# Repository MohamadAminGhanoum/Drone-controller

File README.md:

# Drone-controller
So i have this drone that i have had for a very long time. I recieved it without a controller, so it was basically a uselss drone. I played with it previously and tried to connect all 4 motors to 5v to see if it would fly, but ofc it wouldnt stablilize and all that. Today i know that i need a specific IMU snesor using the gyroscope to determing how the drone is positioned, and then it would send this signal to a chip that would control the current or power recieved by each motor to stabilize the drone. This is what i have planned to make in this project, and it would be slightly more complex than a normal drone controller, as i need to add motor controllers as well because my drone has bruhless motors.

## Schematics for controller:

## Schematics for remote:

## PCB for controller:

## PCB for remote:

## 3d shape for controller:

## 3d shape for remote:

## BOM:

|Nr |Designator                                                      |Footprint                                                          |Quantity                 |Cost, usd|Designation                |Supplier and ref|Link                                                                                                                                                                                                                                                        |
|---|----------------------------------------------------------------|-------------------------------------------------------------------|-------------------------|---------|---------------------------|----------------|------------------------------------------------------------------------------------------------------------------------------------------------------------------------------------------------------------------------------------------------------------|
|1  |U1                                                              |LQFP-64_10x10mm_P0.5mm                                             |3                        |20.86    |STM32F405RGTx              |Lcsc            |https://www.lcsc.com/product-detail/C15742.html?spm=wm.gwc.xh.0.tp___wm.sy.ssl.gwc&lcsc_vid=EQBXBlEAQgcKBVQCEVVYVVZWFAJcV1dXFlJYUFxeRgIxVlNeQ1ddUFZfTlFaVzsOAxUeFF5JWBEPFBcWGBMaSQgFBAJABAsLWA%3D%3D                                                        |
|2  |Fan1,2,3,4                                                      |JST_PH_B2B-PH-K_1x02_P2.00mm_Vertical                              |20                       |0.71     |MOTORs                     |LCSC            |https://www.lcsc.com/product-detail/C131337.html?s_z=n_q_p_JST_PH_B2B-PH-K_1x02_P2.00mm_Vertical&spm=wm.ssy.bg.0.stp&lcsc_vid=EQBXBlEAQgcKBVQCEVVYVVZWFAJcV1dXFlJYUFxeRgIxVlNeQ1ZfUlxSRVJWVjsOAxUeFF5JWBYZEEoKFBINSQcJGk4%3D                                |
|3  |R5,R6                                                           |R_0603_1608Metric                                                  |100                      |0.72     |22                         |LCSC            |https://www.lcsc.com/product-detail/C107701.html?s_z=n_q_t_22ohm%25200603&spm=wm.fly.bg.0.stp___wm.ssy.tc.0.tz&lcsc_vid=EQBXBlEAQgcKBVQCEVVYVVZWFAJcV1dXFlJYUFxeRgIxVlNeQ1ZfUlxfQVZYXjsOAxUeFF5JWBYZEEoKFBINSQcJGk4dAgUUFAk%3D                              |
|4  |L2                                                              |L_Bourns_SRP7028A_7.3x6.6mm                                        |10                       |0.8      |15uH                       |LCSC            |https://www.lcsc.com/product-detail/C5349699.html?spm=wm.gwc.xh.5.tp___wm.sy.ssl.gwc&lcsc_vid=EQBXBlEAQgcKBVQCEVVYVVZWFAJcV1dXFlJYUFxeRgIxVlNeQ1ddUFZfTlFaVzsOAxUeFF5JWBEPFBcWGBMaSQgFBAJABAsLWA%3D%3D                                                      |
|5  |C3,C32,C10,C17,C30,C18,C21,C23,C20,C9,C29,C26,C22,C19,C7,C24,C25|C_0603_1608Metric                                                  |50                       |1.27     |0.1uF                      |LCSC            |https://www.lcsc.com/product-detail/C14663.html?s_z=n_q_t_0.1uF%25200603&spm=wm.fly.bg.0.stp___wm.ssy.tc.0.tz&lcsc_vid=EQBXBlEAQgcKBVQCEVVYVVZWFAJcV1dXFlJYUFxeRgIxVlNeQ1ZfUVdVRlFcVzsOAxUeFF5JWBYZEEoKFBINSQcJGk4eFQsCAgIaSgADAwAHC0slTlNaV1VIHxUDCw%3D%3D |
|6  |C31,C33                                                         |C_0603_1608Metric                                                  |50                       |0.8      |10nF                       |LCSC            |https://www.lcsc.com/product-detail/C100042.html?s_z=n_q_t_10nF%25200603&spm=wm.fly.bg.0.stp___wm.ssy.tc.0.tz&lcsc_vid=EQBXBlEAQgcKBVQCEVVYVVZWFAJcV1dXFlJYUFxeRgIxVlNeQ1ZfUVdQQ1RXUDsOAxUeFF5JWBYZEEoKFBINSQcJGk4NBhADEA4cHktXRlVcSQwSGg0%3D               |
|7  |U7                                                              |XCVR_SX1280IMLTRT                                                  |3                        |12.71    |SX1280IMLTRT               |LCSC            |https://www.lcsc.com/product-detail/C125969.html?spm=wm.gwc.xh.4.tp___wm.sy.ssl.gwc&lcsc_vid=EQBXBlEAQgcKBVQCEVVYVVZWFAJcV1dXFlJYUFxeRgIxVlNeQ1ddUFZfTlFaVzsOAxUeFF5JWBEPFBcWGBMaSQgFBAJABAsLWA%3D%3D                                                       |
|8  |C39                                                             |C_0603_1608Metric                                                  |50                       |0.73     |100pF                      |LCSC            |https://www.lcsc.com/product-detail/C14665.html?s_z=n_q_t_100pF%25200603&spm=wm.fly.bg.0.stp___wm.ssy.tc.0.tz&lcsc_vid=EQBXBlEAQgcKBVQCEVVYVVZWFAJcV1dXFlJYUFxeRgIxVlNeQ1ZfUVdfQlNZXjsOAxUeFF5JWBYZEEoKFBINSQcJGk4eFQsCAgIaSgADAwAHC0slRlFeV1BUWQkaCgg%3D   |
|9  |C34                                                             |C_0603_1608Metric                                                  |20                       |0.62     |470nF                      |LCSC            |https://www.lcsc.com/product-detail/C1623.html?s_z=n_q_t_470nF%25200603&spm=wm.fly.bg.0.stp___wm.ssy.tc.0.tz&lcsc_vid=EQBXBlEAQgcKBVQCEVVYVVZWFAJcV1dXFlJYUFxeRgIxVlNeQ1ZfUVBURFhWVzsOAxUeFF5JWBYZEEoKFBINSQcJGk4dAgUUFAk%3D                                |
|10 |C2,C1,C12,C15                                                   |C_0603_1608Metric                                                  |20                       |0.83     |10uF                       |LCSC            |https://www.lcsc.com/product-detail/C19702.html?s_z=n_q_t_10uF%25200603&spm=wm.fly.bg.0.stp___wm.ssy.tc.0.tz&lcsc_vid=EQBXBlEAQgcKBVQCEVVYVVZWFAJcV1dXFlJYUFxeRgIxVlNeQ1ZfUVBTQlVXUjsOAxUeFF5JWBYZEEoKFBINSQcJGk4eFQsCAgIaSgADAwAHC0slRldcVEoOAwwC          |
|11 |C6,C4,C5                                                        |C_0603_1608Metric                                                  |5                        |0.66     |22uF                       |LCSC            |https://www.lcsc.com/product-detail/C2762594.html?s_z=n_q_t_22uf%25200603&spm=wm.fly.bg.0.stp___wm.ssy.tc.0.tz&lcsc_vid=EQBXBlEAQgcKBVQCEVVYVVZWFAJcV1dXFlJYUFxeRgIxVlNeQ1ZfUVBfQ1VZUTsOAxUeFF5JWBYZEEoKFBINSQcJGk4eFQsCAgIaSgADAwAHC0slRlhZV1ZIHxUDCw%3D%3D|
|12 |U5                                                              |SOT-23-6                                                           |3                        |4        |TPS563200                  |LCSC            |https://www.lcsc.com/product-detail/C97253.html?spm=wm.gwc.xh.2.tp___wm.sy.ssl.gwc&lcsc_vid=EQBXBlEAQgcKBVQCEVVYVVZWFAJcV1dXFlJYUFxeRgIxVlNeQ1ddUFZfTlFaVzsOAxUeFF5JWBEPFBcWGBMaSQgFBAJABAsLWA%3D%3D                                                        |
|13 |C35                                                             |C_0603_1608Metric                                                  |5                        |0.76     |0.8pF                      |LCSC            |https://www.lcsc.com/product-detail/C42432054.html?s_z=n_q_t_0.8pF%25200603&spm=wm.fly.bg.0.stp&lcsc_vid=EQBXBlEAQgcKBVQCEVVYVVZWFAJcV1dXFlJYUFxeRgIxVlNeQ1ZfUVFVRFBaUTsOAxUeFF5JWBYZEEoKFBINSQcJGk4dAgUUFAk%3D                                             |
|14 |U4,U3                                                           |HTSSOP-16-1EP_4.4x5mm_P0.65mm_EP3.4x5mm_Mask2.46x2.31mm_ThermalVias|3                        |3.27     |DRV8833PWP                 |LCSC            |https://www.lcsc.com/product-detail/C50506.html?spm=wm.gwc.dh.1.tp___wm.sy.ssl.gwc&lcsc_vid=EQBXBlEAQgcKBVQCEVVYVVZWFAJcV1dXFlJYUFxeRgIxVlNeQ1ddUFZfTlFaVzsOAxUeFF5JWBEPFBcWGBMaSQgFBAJABAsLWA%3D%3D                                                        |
|15 |J1                                                              |USB_C_Receptacle_GCT_USB4105-xx-A_16P_TopMnt_Horizontal            |2                        |0        |USB_C_Receptacle_USB2.0_16P|Selfsourced     |previously bought from lcsc                                                                                                                                                                                                                                 |
|16 |C16,C11                                                         |C_0603_1608Metric                                                  |50                       |0.8      |0.01uF                     |LCSC            |https://www.lcsc.com/product-detail/C100042.html?s_z=n_q_t_0.01uF%25200603&spm=wm.fly.bg.0.stp&lcsc_vid=EQBXBlEAQgcKBVQCEVVYVVZWFAJcV1dXFlJYUFxeRgIxVlNeQ1ZfUVFQRFBeXjsOAxUeFF5JWBYZEEoKFBINSQcJGk4dAgUUFAk%3D                                              |
|17 |C13,C14,C28                                                     |C_0603_1608Metric                                                  |50                       |1.45     |2.2uF                      |LCSC            |https://www.lcsc.com/product-detail/C23630.html?s_z=n_q_t_2.2uF%25200603&spm=wm.fly.bg.0.stp___wm.ssy.tc.0.tz&lcsc_vid=EQBXBlEAQgcKBVQCEVVYVVZWFAJcV1dXFlJYUFxeRgIxVlNeQ1ZfUVFeQlZZVzsOAxUeFF5JWBYZEEoKFBINSQcJGk4eFQsCAgIaSgADAwAHC0slRlFeV1BUWQkaCgg%3D   |
|18 |R3,R4                                                           |R_0603_1608Metric                                                  |100                      |0.28     |5.1k                       |LCSC            |https://www.lcsc.com/product-detail/C2907044.html?s_z=n_q_t_5.1k%25200603&spm=wm.fly.bg.0.stp___wm.ssy.tc.0.tz&lcsc_vid=EQBXBlEAQgcKBVQCEVVYVVZWFAJcV1dXFlJYUFxeRgIxVlNeQ1ZfUVJXQ1FdVDsOAxUeFF5JWBYZEEoKFBINSQcJGk4NBhADEA4cHktXRlVcSQwSGg0%3D              |
|19 |R7,R2                                                           |R_0603_1608Metric                                                  |100                      |0.81     |10k                        |LCSC            |https://www.lcsc.com/product-detail/C844918.html?s_z=n_q_t_10k%25200603&spm=wm.fly.bg.0.stp___wm.ssy.tc.0.tz&lcsc_vid=EQBXBlEAQgcKBVQCEVVYVVZWFAJcV1dXFlJYUFxeRgIxVlNeQ1ZfUVJSRFhbUzsOAxUeFF5JWBYZEEoKFBINSQcJGk4NBhADEA4cHktXRlhXSQwSGg0%3D                |
|21 |C27                                                             |C_0603_1608Metric                                                  |50                       |1.15     |1uF                        |LCSC            |https://www.lcsc.com/product-detail/C29936.html?s_z=n_q_t_1uF%25200603&spm=wm.fly.bg.0.stp&lcsc_vid=EQBXBlEAQgcKBVQCEVVYVVZWFAJcV1dXFlJYUFxeRgIxVlNeQ1ZfUVJfRVFbXzsOAxUeFF5JWBYZEEoKFBINSQcJGk4dAgUUFAk%3D                                                  |
|22 |D1,D2                                                           |D_SMA                                                              |50                       |0.73     |SS14                       |LCSC            |https://www.lcsc.com/product-detail/C2837270.html?s_z=n_q_x_SS14&spm=wm.ssy.em.0.tz&lcsc_vid=EQBXBlEAQgcKBVQCEVVYVVZWFAJcV1dXFlJYUFxeRgIxVlNeQ1ZfUVNUQFFeVzsOAxUeFF5JWBYZEEoKFBINSQcJGk4NBhADEA4cHktXRlVcSQwSGg0%3D                                         |
|23 |C38                                                             |C_0603_1608Metric                                                  |100                      |0.72     |0.5pF                      |LCSC            |https://www.lcsc.com/product-detail/C1633.html?s_z=n_q_t_0.5pf%25200603&spm=wm.fly.bg.0.stp&lcsc_vid=EQBXBlEAQgcKBVQCEVVYVVZWFAJcV1dXFlJYUFxeRgIxVlNeQ1ZfUVNQRFNWUDsOAxUeFF5JWBYZEEoKFBINSQcJGk4dAgUUFAk%3D                                                 |
|24 |Y2                                                              |Crystal_SMD_3225-4Pin_3.2x2.5mm                                    |5                        |0.51     |52mhz                      |LCSC            |https://www.lcsc.com/product-detail/C3034316.html?s_z=n_q_52%2520mhz%2520crystal&spm=wm.fly.bg.0.stp&lcsc_vid=T1FYAQdRRlJYVlZTQldcX11eQ1FfUlFUElBWUQFVQgIxVlNeQlVWV11eRFZXUzsOAxUeFF5JWBYZEEoKFBINSQcJGk4eFQsCAgIaSgADAwAHC0slQFBWUVFfWQkaCgg%3D            |
|25 |AE1                                                             |U.FL_Hirose_U.FL-R-SMT-1_Vertical                                  |1                        |N/A      |Antenna                    |N/A             |https://www.lcsc.com/product-detail/C88374.html                                                                                                                                                                                                             |
|26 |JBat                                                            |JST_PH_B2B-PH-K_1x02_P2.00mm_Vertical                              |20                       |0.71     |Battery_connector          |LCSC            |https://www.lcsc.com/product-detail/C131337.html?s_z=n_q_p_JST_PH_B2B-PH-K_1x02_P2.00mm_Vertical&spm=wm.ssy.bg.0.stp&lcsc_vid=EQBXBlEAQgcKBVQCEVVYVVZWFAJcV1dXFlJYUFxeRgIxVlNeQ1ZfUlxSRVJWVjsOAxUeFF5JWBYZEEoKFBINSQcJGk4%3D                                |
|27 |L1                                                              |L_Bourns_SRP7028A_7.3x6.6mm                                        |10                       |0.7      |3.3uH                      |LCSC            |https://www.lcsc.com/product-detail/C5349703.html?s_z=n_q_p_3.3uH%25207.1x6.6&spm=wm.ssy.bg.0.stp&lcsc_vid=EQBXBlEAQgcKBVQCEVVYVVZWFAJcV1dXFlJYUFxeRgIxVlNeQ1ZfUV1WR1BWXjsOAxUeFF5JWBYZEEoKFBINSQcJGk4NBhADEA4cHktXRlRbSQwSGg0%3D                           |
|28 |R1                                                              |R_0603_1608Metric                                                  |100                      |0.32     |54.9k                      |LCSC            |https://www.lcsc.com/product-detail/C23077.html?s_z=n_q_p_54.9k%252006043&spm=wm.ssy.bg.1.stp&lcsc_vid=EQBXBlEAQgcKBVQCEVVYVVZWFAJcV1dXFlJYUFxeRgIxVlNeQ1ZfUV1VQVRXUDsOAxUeFF5JWBYZEEoKFBINSQcJGk4eFQsCAgIaSgADAwAHC0slQlJaXlNWRE8GEwkK                     |
|29 |SW1                                                             |R_0603_1608Metric                                                  |1                        |0        |SW_Push                    |Selfsourced     |previously bought from lcsc                                                                                                                                                                                                                                 |
|30 |U6                                                              |SOT95P285X140-5N                                                   |5                        |0.79     |AP2112K-3.3TRG1            |LCSC            |https://www.lcsc.com/product-detail/C51118.html?spm=wm.gwc.xh.3.tp___wm.sy.ssl.gwc&lcsc_vid=EQBXBlEAQgcKBVQCEVVYVVZWFAJcV1dXFlJYUFxeRgIxVlNeQ1ddUFZfTlFaVzsOAxUeFF5JWBEPFBcWGBMaSQgFBAJABAsLWA%3D%3D                                                        |
|31 |U2                                                              |InvenSense_QFN-24_4x4mm_P0.5mm                                     |2                        |29.24    |MPU-6000                   |LCSC            |https://www.lcsc.com/product-detail/C92401.html?s_z=n_q_x_MPU-6000&spm=wm.ssy.em.0.tz&lcsc_vid=EQBXBlEAQgcKBVQCEVVYVVZWFAJcV1dXFlJYUFxeRgIxVlNeQ1ZfUVZSQ1laVTsOAxUeFF5JWBYZEEoKFBINSQcJGk4NBhYS                                                             |
|32 |C8                                                              |C_0603_1608Metric                                                  |50                       |0.63     |2.2nF                      |LCSC            |https://www.lcsc.com/product-detail/C16033.html?s_z=n_q_t_2.2nF%25200603&spm=wm.fly.bg.0.stp___wm.ssy.tc.0.tz&lcsc_vid=EQBXBlEAQgcKBVQCEVVYVVZWFAJcV1dXFlJYUFxeRgIxVlNeQ1ZfUV1QQlRZVDsOAxUeFF5JWBYZEEoKFBINSQcJGk4eFQsCAgIaSgADAwAHC0slRVJeUFNIHxUDCw%3D%3D |
|33 |C37,C36                                                         |C_0603_1608Metric                                                  |100                      |0.68     |1.2pF                      |LCSC            |https://www.lcsc.com/product-detail/C519098.html?s_z=n_q_t_1.2pF%25200603&spm=wm.fly.bg.0.stp___wm.ssy.tc.0.tz&lcsc_vid=EQBXBlEAQgcKBVQCEVVYVVZWFAJcV1dXFlJYUFxeRgIxVlNeQ1ZfUFRWRlBWVDsOAxUeFF5JWBYZEEoKFBINSQcJGk4eFQsCAgIaSgADAwAHC0slRldeVFdIHxUDCw%3D%3D|
|34 |PCB                                                             |Remote controller                                                  |5                        |7        |N/A                        |Jlcpcb          |N/A                                                                                                                                                                                                                                                         |
|35 |PCB                                                             |Drone controller                                                   |5                        |7        |N/A                        |Jlcpcb          |N/A                                                                                                                                                                                                                                                         |
|36 |AE1                                                             |Antenna                                                            |2                        |6.43     |N/A                        |LCSC            |https://www.lcsc.com/product-detail/C3285086.html                                                                                                                                                                                                           |
|37 |C                                                               |C_0603_1608Metric                                                  |50                       |0.7      |15pf                       |LCSC            |https://www.lcsc.com/product-detail/C1644.html?s_z=n_q_t_15pf%25200603&spm=wm.fly.bg.0.stp___wm.ssy.tc.0.tz&lcsc_vid=T1FYAQdRRlJYVlZTQldcX11eQ1FfUlFUElBWUQFVQgIxVlNeQlVXV1ReRlVXVTsOAxUeFF5JWBYZEEoKFBINSQcJGk4eFQsCAgIaSgADAwAHC0slRFNWUlReQU8GEwkK       |
|   |                                                                |                                                                   |                         |         |                           |                |                                                                                                                                                                                                                                                            |
|   |                                                                |                                                                   |Total price w. tax & ship|150.69   |                           |                |                                                                                                                                                                                                                                                            |

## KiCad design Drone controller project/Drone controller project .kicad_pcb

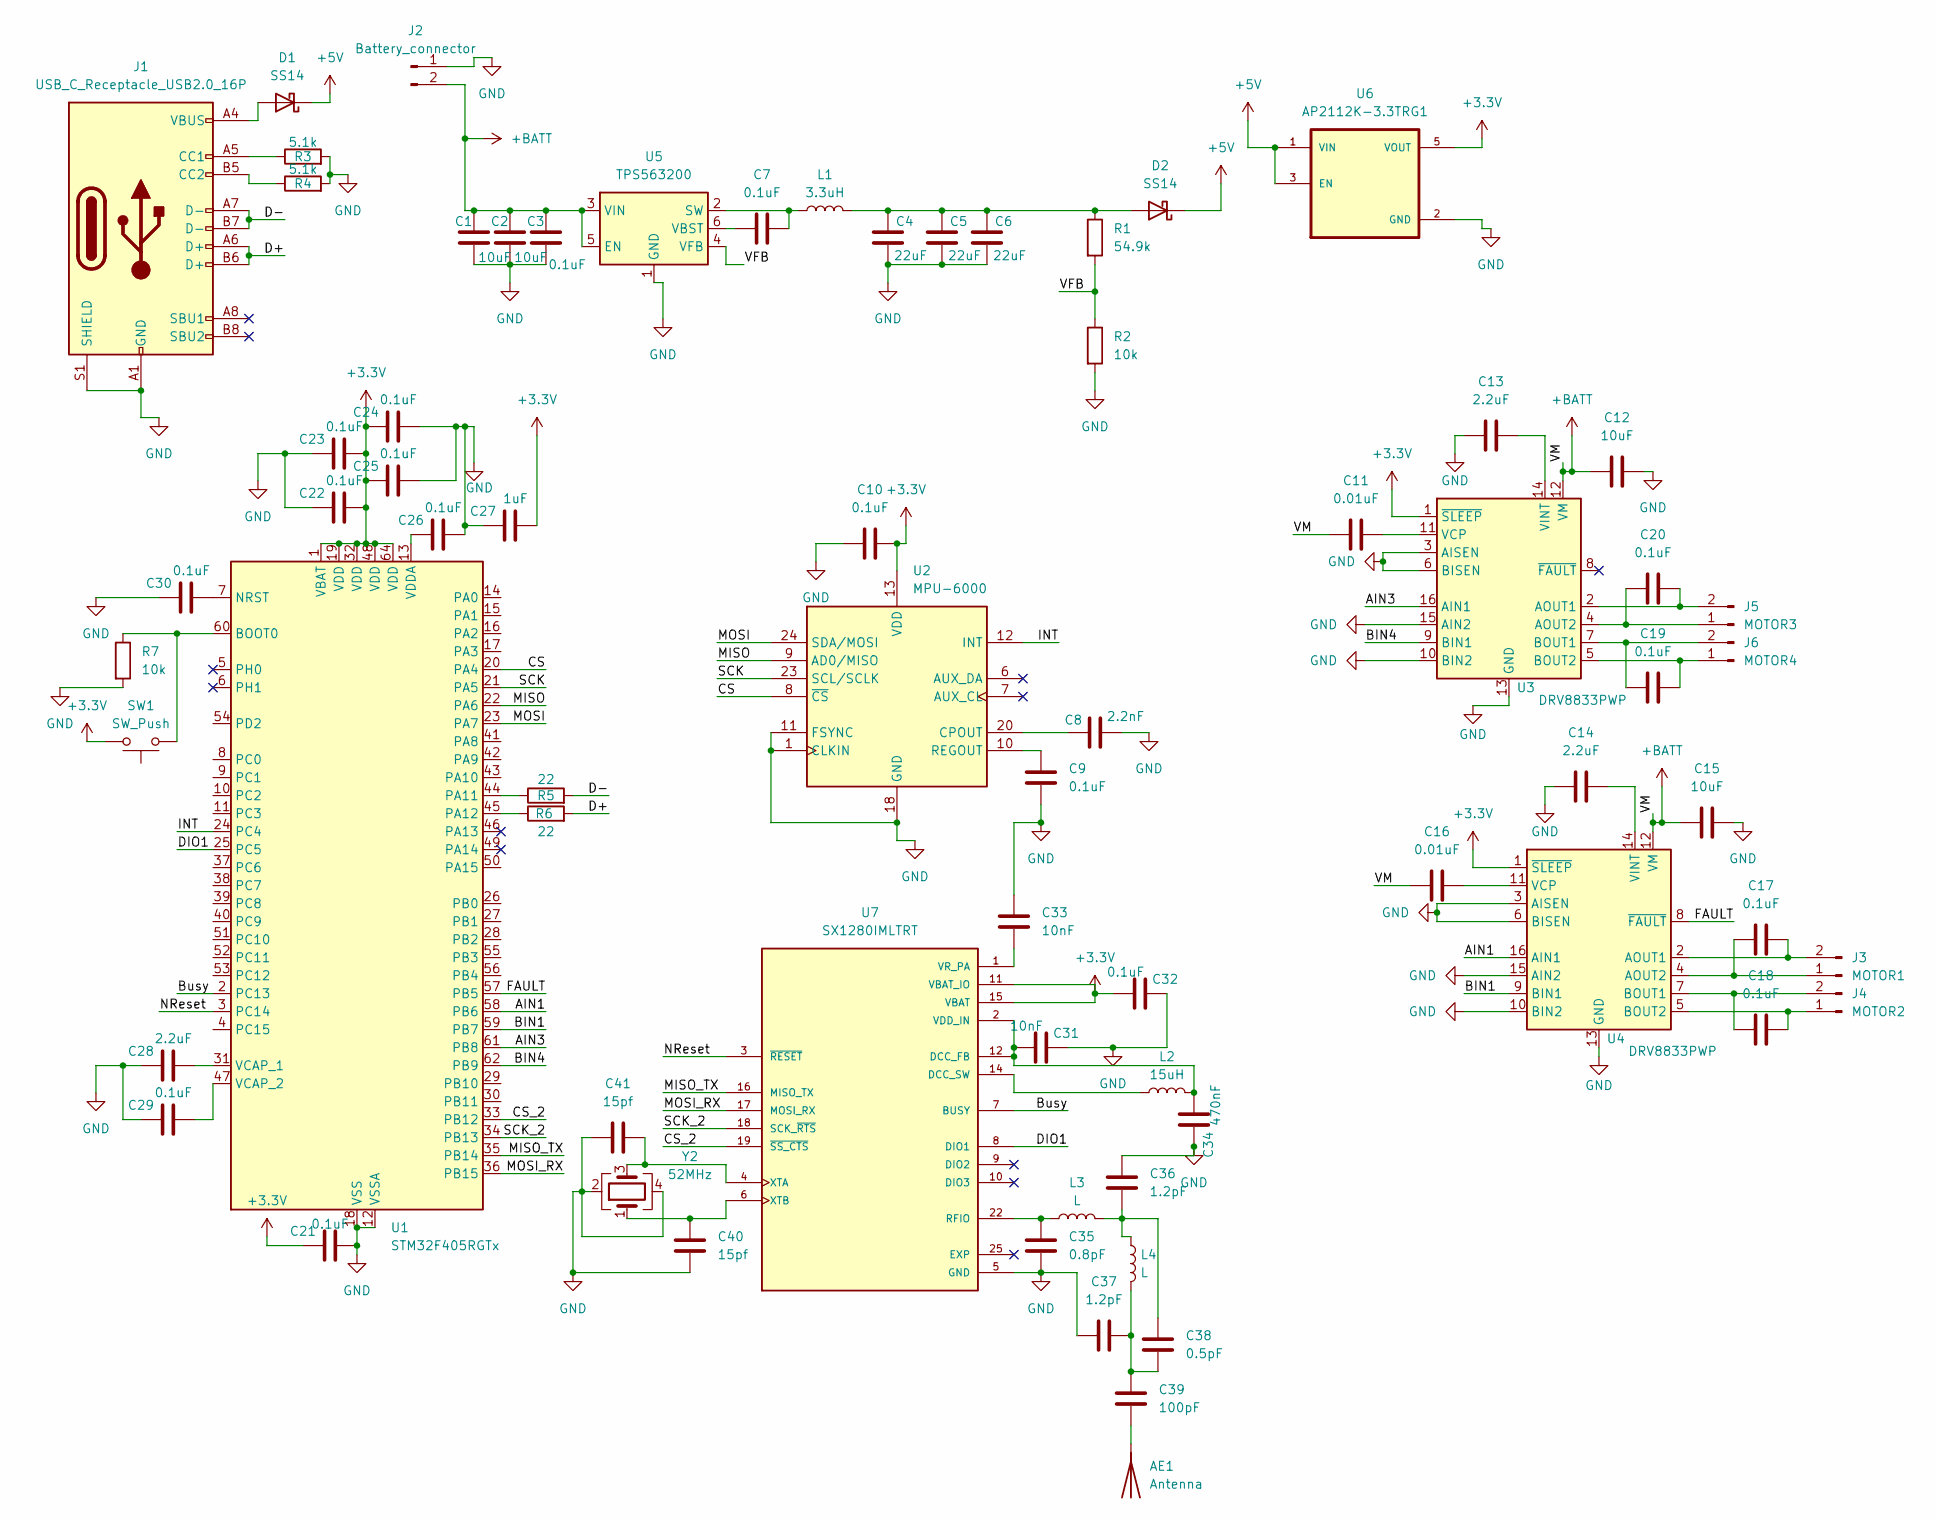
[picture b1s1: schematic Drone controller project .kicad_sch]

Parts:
AE1: Antenna; U.FL_Hirose_U.FL-R-SMT-1_Vertical
C1, C2, C12, C15: 10uF; C_0603_1608Metric
C3, C7, C9, C10, C17, C18, C19, C20, C21, C22, C23, C24, C25, C26, C29, C30, C32: 0.1uF; C_0603_1608Metric
C4, C5, C6: 22uF; C_0603_1608Metric
C8: 2.2nF; C_0603_1608Metric
C11, C16: 0.01uF; C_0603_1608Metric
C13, C14, C28: 2.2uF; C_0603_1608Metric
C27: 1uF; C_0603_1608Metric
C31, C33: 10nF; C_0603_1608Metric
C34: 470nF; C_0603_1608Metric
C35: 0.8pF; C_0603_1608Metric
C36, C37: 1.2pF; C_0603_1608Metric
C38: 0.5pF; C_0603_1608Metric
C39: 100pF; C_0603_1608Metric
C40, C41: 15pf; C_0603_1608Metric
D1, D2: SS14; D_SMA
J1: USB_C_Receptacle_USB2.0_16P; USB_C_Receptacle_GCT_USB4105-xx-A_16P_TopMnt_Horizontal
J2: Battery_connector; JST_PH_B2B-PH-K_1x02_P2.00mm_Vertical
J3: MOTOR1; JST_PH_B2B-PH-K_1x02_P2.00mm_Vertical
J4: MOTOR2; JST_PH_B2B-PH-K_1x02_P2.00mm_Vertical
J5: MOTOR3; JST_PH_B2B-PH-K_1x02_P2.00mm_Vertical
J6: MOTOR4; JST_PH_B2B-PH-K_1x02_P2.00mm_Vertical
L1: 3.3uH; L_Bourns_SRP7028A_7.3x6.6mm
L2: 15uH; L_Bourns_SRP7028A_7.3x6.6mm
L3, L4: L; L_Bourns_SRP7028A_7.3x6.6mm
R1: 54.9k; R_0603_1608Metric
R2, R7: 10k; R_0603_1608Metric
R3, R4: 5.1k; R_0603_1608Metric
R5, R6: 22; R_0603_1608Metric
SW1: SW_Push; R_0603_1608Metric
U1: STM32F405RGTx; LQFP-64_10x10mm_P0.5mm
U2: MPU-6000; InvenSense_QFN-24_4x4mm_P0.5mm
U3, U4: DRV8833PWP; HTSSOP-16-1EP_4.4x5mm_P0.65mm_EP3.4x5mm_Mask2.46x2.31mm_The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
U5: TPS563200; SOT-23-6
U6: AP2112K-3.3TRG1; SOT95P285X140-5N; PARTREV 2-2
U7: SX1280IMLTRT; XCVR_SX1280IMLTRT; PARTREV 3.3
Y2: 52MHz; Crystal_SMD_3225-4Pin_3.2x2.5mm

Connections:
+3.3V: C10.2, C21.1, C22.2, C23.2, C24.1, C25.1, C27.2, C32.1, SW1.2, U1.1 (VBAT), U1.19 (VDD), U1.32 (VDD), U1.48 (VDD), U1.64 (VDD), U2.13 (VDD), U3.1 (~SLEEP), U4.1 (~SLEEP), U6.5 (VOUT), U7.11 (VBAT_IO), U7.15 (VBAT)
+5V: D1.1 (K), D2.1 (K), U6.1 (VIN), U6.3 (EN)
+BATT: C1.1, C2.1, C3.1, C11.1, C12.1, C15.1, C16.1, J2.2, U3.12 (VM), U4.12 (VM), U5.3 (VIN), U5.5 (EN)
/AIN1: U1.58 (PB6), U4.16 (AIN1)
/AIN3: U1.61 (PB8), U3.16 (AIN1)
/BIN1: U1.59 (PB7), U4.9 (BIN1)
/BIN4: U1.62 (PB9), U3.9 (BIN1)
/Busy: U1.2 (PC13), U7.7 (BUSY)
/CS: U1.20 (PA4), U2.8 (~CS)
/CS_2: U1.33 (PB12), U7.19 (~SS_CTS)
/D+: J1.A6 (D+), J1.B6 (D+), R6.2
/D-: J1.A7 (D-), J1.B7 (D-), R5.2
/DIO1: U1.25 (PC5), U7.8 (DIO1)
/FAULT: U1.57 (PB5), U4.8 (~FAULT)
/INT: U1.24 (PC4), U2.12 (INT)
/MISO: U1.22 (PA6), U2.9 (AD0/MISO)
/MISO_TX: U1.35 (PB14), U7.16 (MISO_TX)
/MOSI: U1.23 (PA7), U2.24 (SDA/MOSI)
/MOSI_RX: U1.36 (PB15), U7.17 (MOSI_RX)
/NReset: U1.3 (PC14), U7.3 (~RESET)
/SCK: U1.21 (PA5), U2.23 (SCL/SCLK)
/SCK_2: U1.34 (PB13), U7.18 (SCK_~RTS)
/VFB: R1.2, R2.1, U5.4 (VFB)
GND: C1.2, C2.2, C3.2, C4.2, C5.2, C6.2, C8.2, C9.2, C10.1, C12.2, C13.1, C14.1, C15.2, C21.2, C22.1, C23.1, C24.2, C25.2, C26.2, C27.1, C28.1, C29.1, C30.1, C31.2, C32.2, C33.1, C34.2, C35.2, C36.1, C37.2, C40.2, C41.1, J1.A1 (GND), J1.A12 (GND), J1.B1 (GND), J1.B12 (GND), J1.S1 (SHIELD), J2.1, R2.2, R3.2, R4.2, R7.2, U1.12 (VSSA), U1.18 (VSS), U1.63 (VSS), U2.1 (CLKIN), U2.11 (FSYNC), U2.18 (GND), U3.3 (AISEN), U3.6 (BISEN), U3.10 (BIN2), U3.13 (GND), U3.15 (AIN2), U3.17 (GND), U4.3 (AISEN), U4.6 (BISEN), U4.10 (BIN2), U4.13 (GND), U4.15 (AIN2), U4.17 (GND), U5.1 (GND), U6.2 (GND), U7.5 (GND), U7.13 (GND), U7.20 (GND), U7.21 (GND), U7.23 (GND), U7.24 (GND), Y2.2, Y2.4
unnamed: AE1.1 (A), C39.2
unnamed: C36.2, C38.1, L3.2, L4.1
unnamed: C37.1, C38.2, C39.1, L4.2
unnamed: D1.2 (A), J1.A4 (VBUS), J1.A9 (VBUS), J1.B4 (VBUS), J1.B9 (VBUS)
unnamed: C4.1, C5.1, C6.1, D2.2 (A), L1.2, R1.1
unnamed: J1.A5 (CC1), R3.1
unnamed: J1.B5 (CC2), R4.1
unnamed: C17.1, J3.1, U4.4 (AOUT2)
unnamed: C17.2, J3.2, U4.2 (AOUT1)
unnamed: C18.1, J4.1, U4.5 (BOUT2)
unnamed: C18.2, J4.2, U4.7 (BOUT1)
unnamed: C20.1, J5.1, U3.4 (AOUT2)
unnamed: C20.2, J5.2, U3.2 (AOUT1)
unnamed: C19.2, J6.1, U3.5 (BOUT2)
unnamed: C19.1, J6.2, U3.7 (BOUT1)
unnamed: R7.1, SW1.1, U1.60 (BOOT0)
unnamed: C30.2, U1.7 (NRST)
unnamed: R5.1, U1.44 (PA11)
unnamed: R6.1, U1.45 (PA12)
unnamed: C28.2, U1.31 (VCAP_1)
unnamed: C29.2, U1.47 (VCAP_2)
unnamed: C26.1, U1.13 (VDDA)
unnamed: C8.1, U2.20 (CPOUT)
unnamed: C9.1, U2.10 (REGOUT)
unnamed: C11.2, U3.11 (VCP)
unnamed: C13.2, U3.14 (VINT)
unnamed: C16.2, U4.11 (VCP)
unnamed: C14.2, U4.14 (VINT)
unnamed: C7.2, L1.1, U5.2 (SW)
unnamed: C7.1, U5.6 (VBST)
unnamed: C31.1, C34.1, L2.2, U7.2 (VDD_IN), U7.12 (DCC_FB)
unnamed: L2.1, U7.14 (DCC_SW)
unnamed: C35.1, L3.1, U7.22 (RFIO)
unnamed: C33.2, U7.1 (VR_PA)
unnamed: C41.2, U7.4 (XTA), Y2.3
unnamed: C40.1, U7.6 (XTB), Y2.1

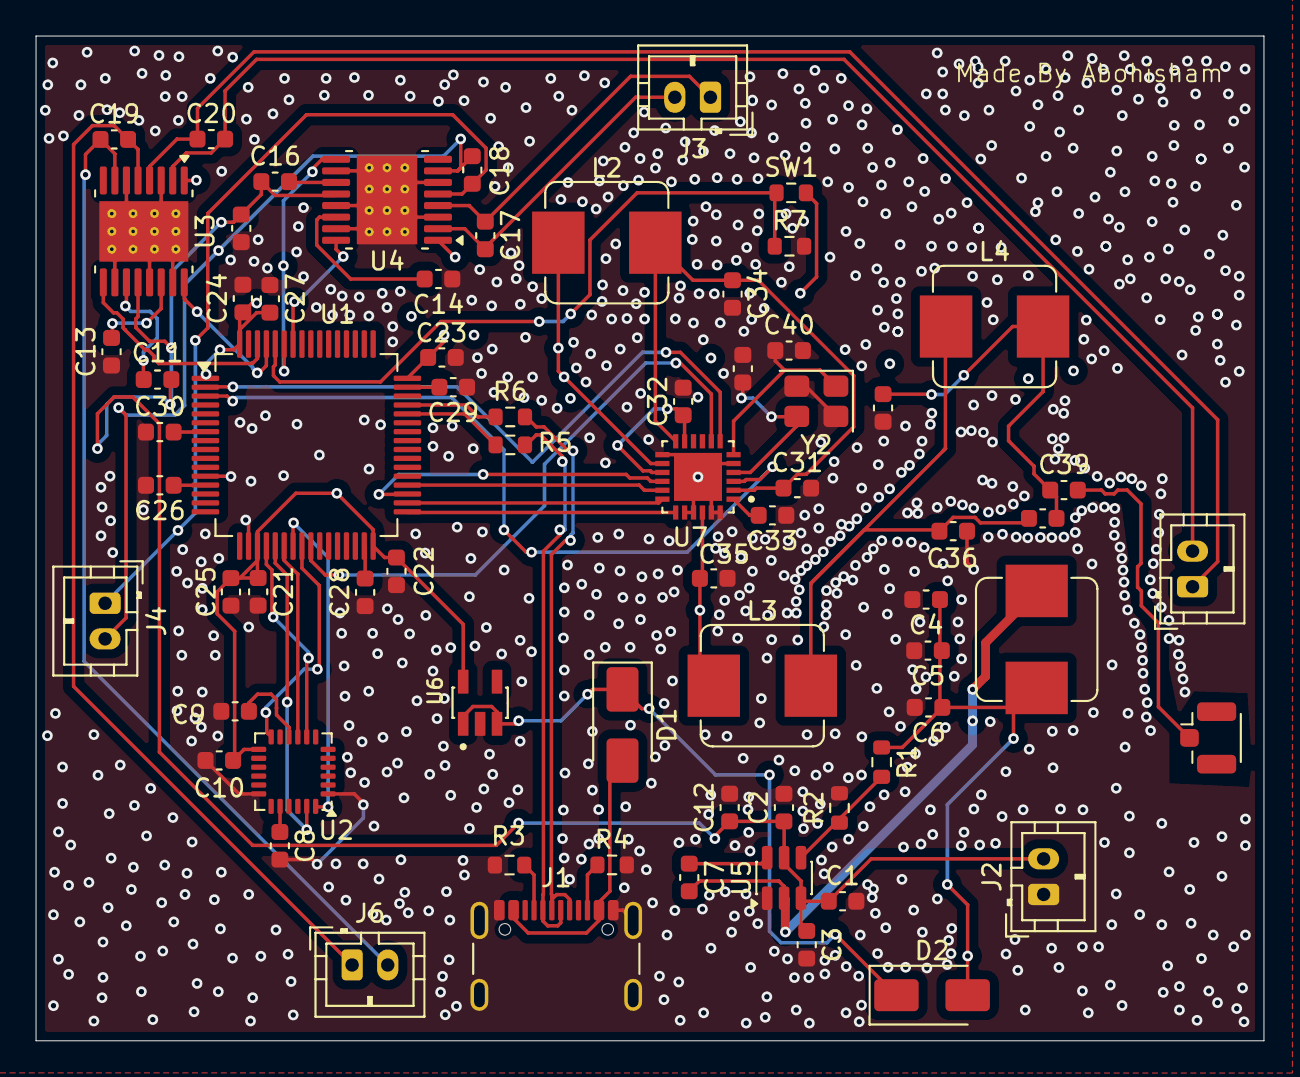
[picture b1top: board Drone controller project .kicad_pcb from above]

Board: 4 copper layers, 69.0 x 56.4 mm, 70 parts (0 on the bottom side), 60 nets.

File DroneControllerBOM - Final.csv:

Nr,Designator,Footprint,Quantity,"Cost, usd",Designation,Supplier and ref,Link
1,U1,LQFP-64_10x10mm_P0.5mm,3,20.86,STM32F405RGTx,Lcsc,https://www.lcsc.com/product-detail/C15742.html?spm=wm.gwc.x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
2,"Fan1,2,3,4",JST_PH_B2B-PH-K_1x02_P2.00mm_Vertical,20,0.71,MOTORs,LCSC,https://www.lcsc.com/product-detail/C131337.html?s_z=n_q_p_J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
3,"R5,R6",R_0603_1608Metric,100,0.72,22,LCSC,https://www.lcsc.com/product-detail/C107701.html?s_z=n_q_t_2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
4,L2,L_Bourns_SRP7028A_7.3x6.6mm,10,0.8,15uH,LCSC,https://www.lcsc.com/product-detail/C5349699.html?spm=wm.gwc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
5,"C3,C32,C10,C17,C30,C18,C21,C23,C20,C9,C29,C26,C22,C19,C7,C24,C25",C_0603_1608Metric,50,1.27,0.1uF,LCSC,https://www.lcsc.com/product-detail/C14663.html?s_z=n_q_t_0.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
6,"C31,C33",C_0603_1608Metric,50,0.8,10nF,LCSC,https://www.lcsc.com/product-detail/C100042.html?s_z=n_q_t_1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
7,U7,XCVR_SX1280IMLTRT,3,12.71,SX1280IMLTRT,LCSC,https://www.lcsc.com/product-detail/C125969.html?spm=wm.gwc.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
8,C39,C_0603_1608Metric,50,0.73,100pF,LCSC,https://www.lcsc.com/product-detail/C14665.html?s_z=n_q_t_10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
9,C34,C_0603_1608Metric,20,0.62,470nF,LCSC,https://www.lcsc.com/product-detail/C1623.html?s_z=n_q_t_470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
10,"C2,C1,C12,C15",C_0603_1608Metric,20,0.83,10uF,LCSC,https://www.lcsc.com/product-detail/C19702.html?s_z=n_q_t_10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
11,"C6,C4,C5",C_0603_1608Metric,5,0.66,22uF,LCSC,https://www.lcsc.com/product-detail/C2762594.html?s_z=n_q_t_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
12,U5,SOT-23-6,3,4,TPS563200,LCSC,https://www.lcsc.com/product-detail/C97253.html?spm=wm.gwc.x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
13,C35,C_0603_1608Metric,5,0.76,0.8pF,LCSC,https://www.lcsc.com/product-detail/C42432054.html?s_z=n_q_t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
14,"U4,U3",HTSSOP-16-1EP_4.4x5mm_P0.65mm_EP3.4x5mm_Mask2.46x2.31mm_ThermalVias,3,3.27,DRV8833PWP,LCSC,https://www.lcsc.com/product-detail/C50506.html?spm=wm.gwc.d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
15,J1,USB_C_Receptacle_GCT_USB4105-xx-A_16P_TopMnt_Horizontal,2,0,USB_C_Receptacle_USB2.0_16P,Selfsourced,previously bought from lcsc
16,"C16,C11",C_0603_1608Metric,50,0.8,0.01uF,LCSC,https://www.lcsc.com/product-detail/C100042.html?s_z=n_q_t_0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
17,"C13,C14,C28",C_0603_1608Metric,50,1.45,2.2uF,LCSC,https://www.lcsc.com/product-detail/C23630.html?s_z=n_q_t_2.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
18,"R3,R4",R_0603_1608Metric,100,0.28,5.1k,LCSC,https://www.lcsc.com/product-detail/C2907044.html?s_z=n_q_t_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
19,"R7,R2",R_0603_1608Metric,100,0.81,10k,LCSC,https://www.lcsc.com/product-detail/C844918.html?s_z=n_q_t_1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
21,C27,C_0603_1608Metric,50,1.15,1uF,LCSC,https://www.lcsc.com/product-detail/C29936.html?s_z=n_q_t_1u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
22,"D1,D2",D_SMA,50,0.73,SS14,LCSC,https://www.lcsc.com/product-detail/C2837270.html?s_z=n_q_x_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
23,C38,C_0603_1608Metric,100,0.72,0.5pF,LCSC,https://www.lcsc.com/product-detail/C1633.html?s_z=n_q_t_0.5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
24,Y2,Crystal_SMD_3225-4Pin_3.2x2.5mm,5,0.51,52mhz,LCSC,https://www.lcsc.com/product-detail/C3034316.html?s_z=n_q_52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
25,AE1,U.FL_Hirose_U.FL-R-SMT-1_Vertical,1,N/A,Antenna,N/A,https://www.lcsc.com/product-detail/C88374.html
26,JBat,JST_PH_B2B-PH-K_1x02_P2.00mm_Vertical,20,0.71,Battery_connector,LCSC,https://www.lcsc.com/product-detail/C131337.html?s_z=n_q_p_J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
27,L1,L_Bourns_SRP7028A_7.3x6.6mm,10,0.7,3.3uH,LCSC,https://www.lcsc.com/product-detail/C5349703.html?s_z=n_q_p_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
28,R1,R_0603_1608Metric,100,0.32,54.9k,LCSC,https://www.lcsc.com/product-detail/C23077.html?s_z=n_q_p_54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
29,SW1,R_0603_1608Metric,1,0,SW_Push,Selfsourced,previously bought from lcsc
30,U6,SOT95P285X140-5N,5,0.79,AP2112K-3.3TRG1,LCSC,https://www.lcsc.com/product-detail/C51118.html?spm=wm.gwc.x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
31,U2,InvenSense_QFN-24_4x4mm_P0.5mm,2,29.24,MPU-6000,LCSC,https://www.lcsc.com/product-detail/C92401.html?s_z=n_q_x_MP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
32,C8,C_0603_1608Metric,50,0.63,2.2nF,LCSC,https://www.lcsc.com/product-detail/C16033.html?s_z=n_q_t_2.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
33,"C37,C36",C_0603_1608Metric,100,0.68,1.2pF,LCSC,https://www.lcsc.com/product-detail/C519098.html?s_z=n_q_t_1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
34,PCB,Remote controller,5,7,N/A,Jlcpcb,N/A
35,PCB,Drone controller,5,7,N/A,Jlcpcb,N/A
36,AE1,Antenna,2,6.43,N/A,LCSC,https://www.lcsc.com/product-detail/C3285086.html
37,C,C_0603_1608Metric,50,0.7,15pf,LCSC,https://www.lcsc.com/product-detail/C1644.html?s_z=n_q_t_15p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
,,,,,,,
,,,Total price w. tax & ship,150.69,,,
